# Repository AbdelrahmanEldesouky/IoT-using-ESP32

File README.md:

# IoT using ESP32 for Home Control 

## Software 

Programming nodeMCU-32S using [Arduino code](Home_Control/Software/HomeControl/HomeControl.ino) to connect with io.adafruit platform using MQTT protocol 

## Hardware

### Component 

1. nodeMCU-ESP32S
2. BT139 
3. MOC3022m 
4. PIR Sensor
5. DHT11 
6. LDR 

Check [data sheet](Home_Control/Hardware/Datasheet) for used components. 

### Schematic 

### Layout 

### Prototype

### PCB 3D View

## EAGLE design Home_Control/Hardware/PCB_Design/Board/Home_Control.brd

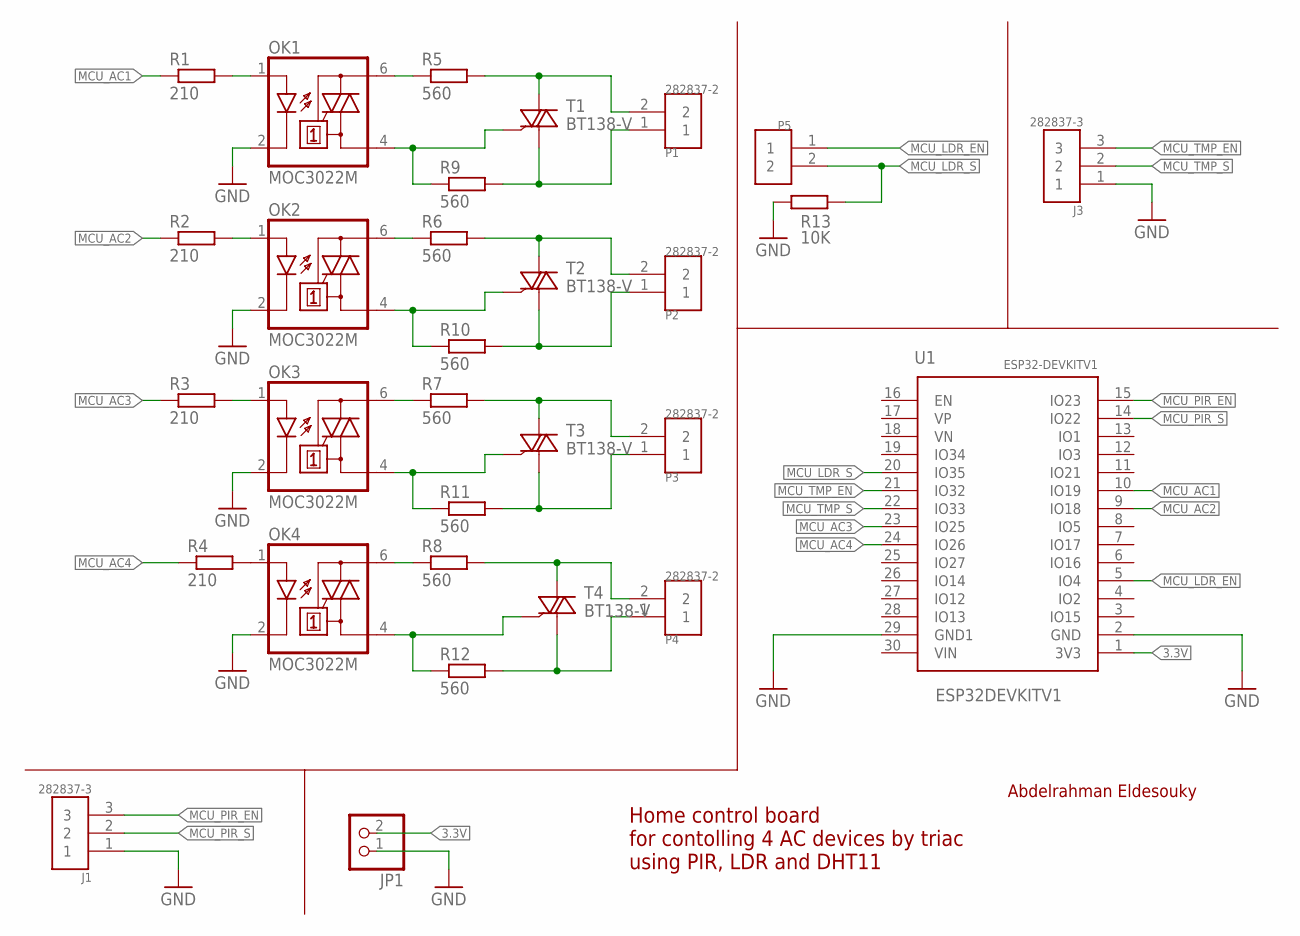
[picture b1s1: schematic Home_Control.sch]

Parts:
J1, J3: 282837-3; TE_282837-3
JP1: PINHD-1X2; 1X02
OK1, OK2, OK3, OK4: MOC3022M; DIL06
P1, P2, P3, P4, P5: 282837-2; TE_282837-2
R1, R2, R3, R4: 210; 0411/15
R5, R6, R7, R8, R9, R10, R11, R12: 560; 0411/15
R13: 10K; 0411/15
T1, T2, T3, T4: BT138-V; TO220BV
U1: ESP32DEVKITV1; ESP32-DEVKITV1

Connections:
3.3V: JP1.2, U1.1 (3V3)
GND: J1.1, J3.1, JP1.1, OK1.2 (C), OK2.2 (C), OK3.2 (C), OK4.2 (C), R13.1, U1.2 (GND), U1.29 (GND1)
MCU_AC1: R1.1, U1.10 (IO19)
MCU_AC2: R2.1, U1.9 (IO18)
MCU_AC3: R3.1, U1.23 (IO25)
MCU_AC4: R4.1, U1.24 (IO26)
MCU_LDR_EN: P5.1, U1.5 (IO4)
MCU_LDR_S: P5.2, R13.2, U1.20 (IO35)
MCU_PIR_EN: J1.3, U1.15 (IO23)
MCU_PIR_S: J1.2, U1.14 (IO22)
MCU_TMP_EN: J3.3, U1.21 (IO32)
MCU_TMP_S: J3.2, U1.22 (IO33)
unnamed: OK1.1 (A), R1.2
unnamed: OK2.1 (A), R2.2
unnamed: OK3.1 (A), R3.2
unnamed: OK4.1 (A), R4.2
unnamed: OK1.4 (A1), R9.1, T1.G
unnamed: OK2.4 (A1), R10.1, T2.G
unnamed: OK3.4 (A1), R11.1, T3.G
unnamed: OK4.4 (A1), R12.1, T4.G
unnamed: OK1.6 (A2), R5.1
unnamed: P1.2, R5.2, T1.T2 (A2)
unnamed: OK2.6 (A2), R6.1
unnamed: P2.2, R6.2, T2.T2 (A2)
unnamed: OK3.6 (A2), R7.1
unnamed: P3.2, R7.2, T3.T2 (A2)
unnamed: OK4.6 (A2), R8.1
unnamed: P4.2, R8.2, T4.T2 (A2)
unnamed: P1.1, R9.2, T1.T1 (A1)
unnamed: P2.1, R10.2, T2.T1 (A1)
unnamed: P3.1, R11.2, T3.T1 (A1)
unnamed: P4.1, R12.2, T4.T1 (A1)

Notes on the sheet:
Abdelrahman Eldesouky
Home control board for contolling 4 AC devices by triac using PIR, LDR and DHT11

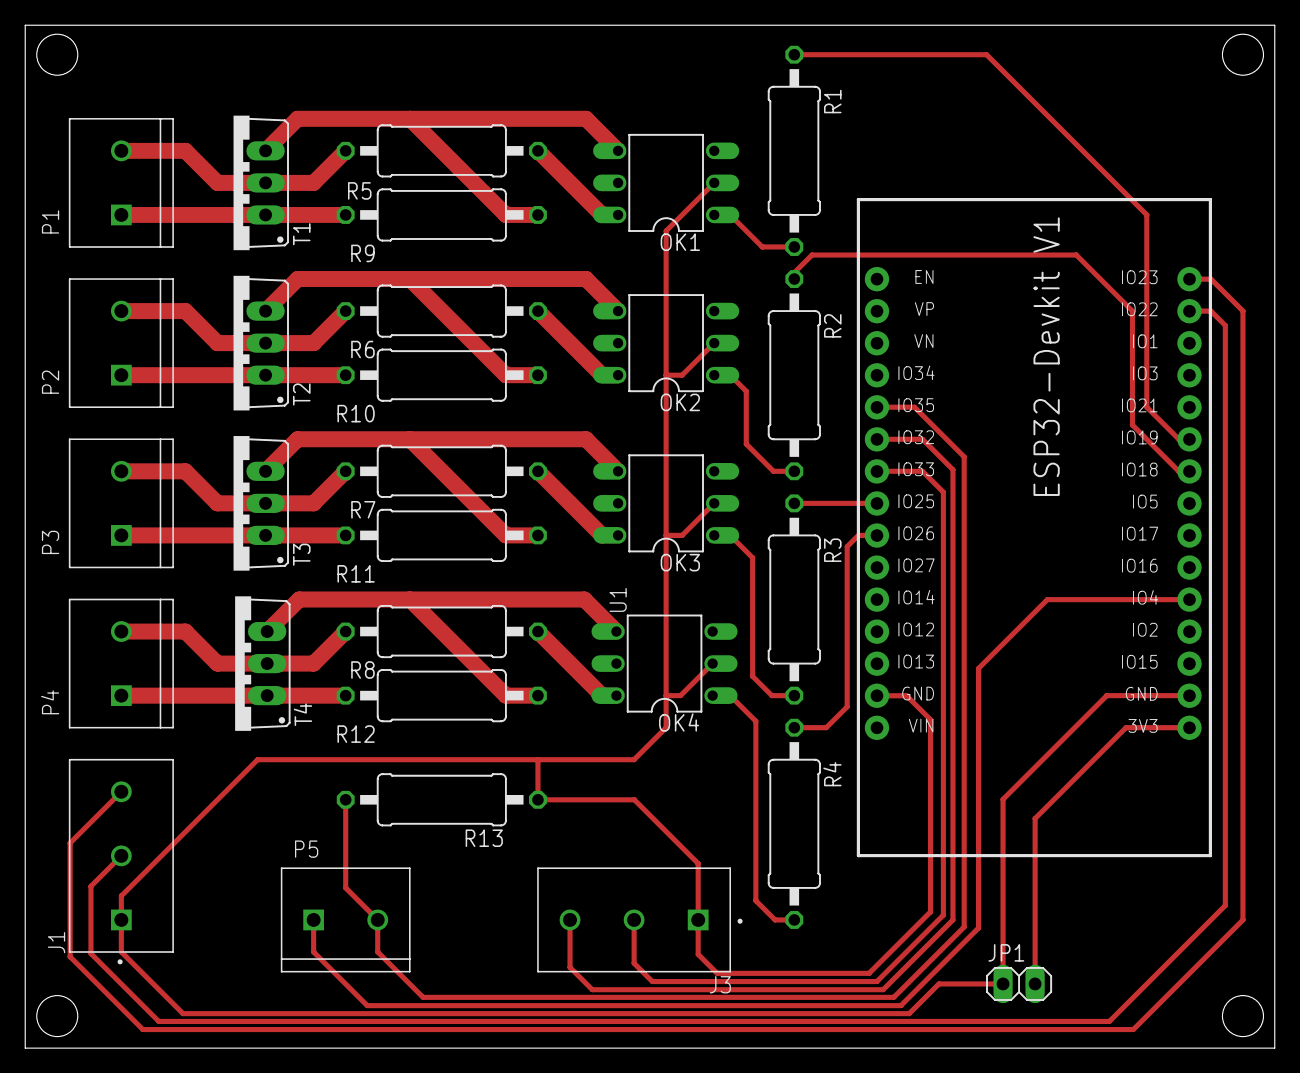
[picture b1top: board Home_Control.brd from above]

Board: 2 copper layers, 99.0 x 81.1 mm, 30 parts (0 on the bottom side), 32 nets.

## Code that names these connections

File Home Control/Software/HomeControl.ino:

#include <WiFi.h>
#include "Adafruit_MQTT.h"
#include "Adafruit_MQTT_Client.h"
#include "DHT.h"


/************************ wifi setup ************************/
#define WIFI_SSID       "Desoky"
#define WIFI_PASSWORD   "12345678"

/************************ MQTT setup ************************/
#define IO_SERVER       "io.adafruit.com"
#define IO_SERVERPORT   1883
#define IO_USERNAME     "AbdelrahmanEldesouky"
#define IO_KEY          "aio_gVsC40dHezneCN3UspjPLa8h16u1"

// Setup the MQTT client class by passing in the WiFi client and MQTT server and login details.
WiFiClient client;
Adafruit_MQTT_Client mqtt(&client, IO_SERVER, IO_SERVERPORT, IO_USERNAME, IO_KEY);
Adafruit_MQTT_Publish TMP = Adafruit_MQTT_Publish(&mqtt, IO_USERNAME "/feeds/TMP");
Adafruit_MQTT_Publish HUM = Adafruit_MQTT_Publish(&mqtt, IO_USERNAME "/feeds/HUM");
Adafruit_MQTT_Publish PIR = Adafruit_MQTT_Publish(&mqtt, IO_USERNAME "/feeds/PIR");
Adafruit_MQTT_Publish LDR = Adafruit_MQTT_Publish(&mqtt, IO_USERNAME "/feeds/LDR");
Adafruit_MQTT_Subscribe AC1 = Adafruit_MQTT_Subscribe(&mqtt, IO_USERNAME "/feeds/AC1", MQTT_QOS_1);
Adafruit_MQTT_Subscribe AC2 = Adafruit_MQTT_Subscribe(&mqtt, IO_USERNAME "/feeds/AC2", MQTT_QOS_1);
Adafruit_MQTT_Subscribe AC3 = Adafruit_MQTT_Subscribe(&mqtt, IO_USERNAME "/feeds/AC3", MQTT_QOS_1);
Adafruit_MQTT_Subscribe AC4 = Adafruit_MQTT_Subscribe(&mqtt, IO_USERNAME "/feeds/AC4", MQTT_QOS_1);


/************************ pin connection ************************/
#define MCU_PIR_EN 23
#define MCU_PIR_S 22
#define MCU_LDR_EN 32
#define MCU_LDR_S 33
#define MCU_TMP_EN 27
#define MCU_TMP_S 13
#define MCU_AC1 19
#define MCU_AC2 18
#define MCU_AC3 25
#define MCU_AC4 26


#define TMP_TYPE DHT11
DHT dht(MCU_TMP_S, TMP_TYPE);

bool isConnected{false};
bool isMoved{false};
bool isCallBack {false} ; 

long int NOW_t ; 
long int LDR_t ;
long int TMP_t ; 
long int PIR_t ; 

// connect to adafruit io via MQTT
void connect() {
  Serial.print(F("Connecting to Adafruit IO... "));
  int8_t ret;
  while ((ret = mqtt.connect()) != 0) 
  {
    switch (ret) 
    {
      case 1: Serial.println(F("Wrong protocol")); break;
      case 2: Serial.println(F("ID rejected")); break;
      case 3: Serial.println(F("Server unavail")); break;
      case 4: Serial.println(F("Bad user/pass")); break;
      case 5: Serial.println(F("Not authed")); break;
      case 6: Serial.println(F("Failed to subscribe")); break;
      default: Serial.println(F("Connection failed")); break;
    }

    if(ret >= 0)
      mqtt.disconnect();

    Serial.println(F("Retrying connection..."));
    delay(10000);
  }
  Serial.println(F("Adafruit IO Connected!"));
}

void read_TMP_HUM()
{
  if ((millis() - TMP_t) > 10000)
  {
    /************************ TMP Sensor ************************/
    // Reading temperature or humidity takes about 250 milliseconds!
    // Sensor readings may also be up to 2 seconds 'old' (its a very slow sensor)
    float h = dht.readHumidity();
    // Read temperature as Celsius (the default)
    float t = dht.readTemperature();
    
    // Check if any reads failed and exit early (to try again).
    if (isnan(h) || isnan(t)) 
    {
      Serial.println(F("Failed to read from DHT sensor!"));
      return;
    }
    
    Serial.print(F("Humidity: "));
    Serial.print(h);
    Serial.print(F("%  Temperature: "));
    Serial.print(t);
    Serial.print(F("°C "));
    
    if (! TMP.publish(t)) //Publish to Adafruit
    {                     
      Serial.println(F("Failed"));
    } 
    if (! HUM.publish(h)) //Publish to Adafruit
    {                     
      Serial.println(F("Failed"));
    }
    else 
    {
      Serial.println(F("Sent!"));
    }

    TMP_t = millis() ;
  }
}
void read_LDR()
{
  /************************ Light Sensor ************************/
  if ((millis() - LDR_t) > 10000)
  {
    // Reading Light Sensor
    double light = ((double)analogRead(MCU_LDR_S)/ 4096.0) * 100.0 ; 
  
    Serial.print(F("Light Percentage: "));
    Serial.print(light);
    Serial.print(F("%  "));
  
    if (! LDR.publish(light)) //Publish to Adafruit
    {                     
      Serial.println(F("Failed"));
    } 
    else 
    {
      Serial.println(F("Sent!"));
    }

    LDR_t = millis() ;
  }
}
void callBack_PIR()
{
  isMoved = true ; 
  isCallBack = true ; 
  PIR_t = millis() ; 
}

void read_PIR()
{
  /************************ Motion Sensor ************************/
  
  if (((millis() - PIR_t) > 3000) && isCallBack)
  {
    Serial.print(F("Motion detected!  "));
    
    if (! PIR.publish(1)) //Publish to Adafruit
    {                     
      Serial.println(F("Failed"));
    } 
    else 
    {
      Serial.println(F("Sent!"));
    }
    
    isCallBack = false ;
  }
  else if (((millis() - PIR_t) > 10000) && isMoved)
  {
    Serial.print(F("Motion stoped...  "));

    if (! PIR.publish(0)) //Publish to Adafruit
    {                     
      Serial.println(F("Failed"));
    } 
    else 
    {
      Serial.println(F("Sent!"));
    }
    
    isMoved = false ;
  }
}

void AC1_callBack(char *data, uint16_t len)
{
  Serial.print("Hey we're in a AC1 callback, the button value is: ");
  Serial.println(data);

  if (*data == '1')
  {
    digitalWrite(MCU_AC1, HIGH); 
  }
  else 
  {
    digitalWrite(MCU_AC1, LOW); 
  }
}

void AC2_callBack(char *data, uint16_t len)
{
  Serial.print("Hey we're in a AC2 callback, the button value is: ");
  Serial.println(data);

  if (*data == '1')
  {
    digitalWrite(MCU_AC2, HIGH); 
  }
  else 
  {
    digitalWrite(MCU_AC2, LOW); 
  }
}

void AC3_callBack(char *data, uint16_t len)
{
  Serial.print("Hey we're in a AC3 callback, the button value is: ");
  Serial.println(data);

  if (*data == '1')
  {
    digitalWrite(MCU_AC3, HIGH); 
  }
  else 
  {
    digitalWrite(MCU_AC3, LOW); 
  }
}

void AC4_callBack(char *data, uint16_t len)
{
  Serial.print("Hey we're in a AC4 callback, the button value is: ");
  Serial.println(data);

  if (*data == '1')
  {
    digitalWrite(MCU_AC4, HIGH); 
  }
  else 
  {
    digitalWrite(MCU_AC4, LOW); 
  }
}

void setup() 
{
  Serial.begin(9600);
  
  pinMode(LED_BUILTIN, OUTPUT);

  WiFi.begin(WIFI_SSID, WIFI_PASSWORD);

  Serial.println("starting");

  while(WiFi.status() != WL_CONNECTED)
  {
    Serial.println(".");
    digitalWrite(LED_BUILTIN, !digitalRead(LED_BUILTIN));
    delay(1000);
    isConnected = false;
  }

  pinMode(MCU_TMP_EN, OUTPUT) ;
  digitalWrite(MCU_TMP_EN, HIGH) ; 
  pinMode(MCU_LDR_EN, OUTPUT) ;
  digitalWrite(MCU_LDR_EN, HIGH) ; 
  pinMode(MCU_PIR_EN, OUTPUT) ;
  digitalWrite(MCU_PIR_EN, HIGH) ;
  pinMode(MCU_PIR_S, INPUT);
  pinMode(MCU_AC1, OUTPUT) ;
  pinMode(MCU_AC2, OUTPUT) ;
  pinMode(MCU_AC3, OUTPUT) ;
  pinMode(MCU_AC4, OUTPUT) ;
  delay (1000);

  // Set motionSensor pin as interrupt, assign interrupt function and set RISING mode
  attachInterrupt(digitalPinToInterrupt(MCU_PIR_S), callBack_PIR, RISING);

  AC1.setCallback(AC1_callBack);
  mqtt.subscribe(&AC1);

  AC2.setCallback(AC2_callBack);
  mqtt.subscribe(&AC2);

  AC3.setCallback(AC3_callBack);
  mqtt.subscribe(&AC3);

  AC4.setCallback(AC4_callBack);
  mqtt.subscribe(&AC4);

  dht.begin();

  LDR_t = millis() ;
  TMP_t = millis() ;  
}

void loop() 
{
  /************************ wifi connection ************************/
  if ((WiFi.status() == WL_CONNECTED) && !isConnected) 
  {
    Serial.println("Connected");
    digitalWrite(LED_BUILTIN, HIGH);
    isConnected = true;

    connect();
  }
  else if (WiFi.status() != WL_CONNECTED)
  {
    Serial.println("reconected...");
    while (WiFi.status() != WL_CONNECTED)
    {
      WiFi.begin(WIFI_SSID, WIFI_PASSWORD);
      Serial.println(".");
      digitalWrite(LED_BUILTIN, !digitalRead(LED_BUILTIN));
      delay(1000);
    }
   isConnected = false;
  }

  /************************ mqtt connection ************************/
  if(! mqtt.ping(3)) 
  {
    // reconnect to adafruit io
    if(! mqtt.connected())
    connect();
  }

  read_TMP_HUM() ;
  read_LDR() ;
  read_PIR() ;
  mqtt.processPackets(1000);
}
